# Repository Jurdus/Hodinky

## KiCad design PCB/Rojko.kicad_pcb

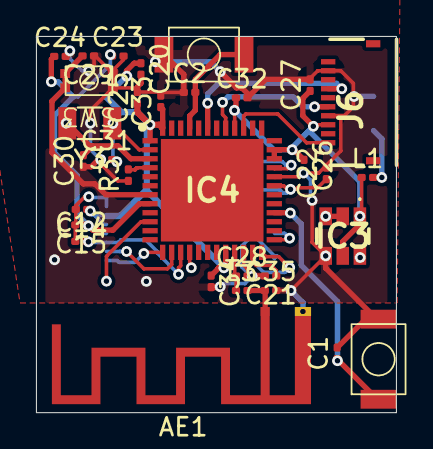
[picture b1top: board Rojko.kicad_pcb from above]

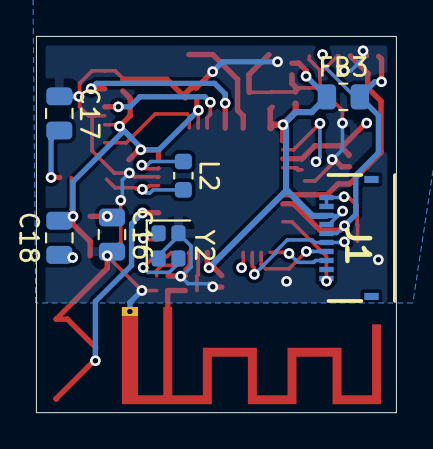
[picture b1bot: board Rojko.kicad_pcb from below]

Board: 2 copper layers, 20.0 x 20.9 mm, 39 parts (7 on the bottom side), 28 nets.

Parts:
AE1: PCB antenna; Texas_SWRA117D_2.4GHz_Right
C1, C2, C29: 100nF; C_0201_0603Metric
C12: 0.1uF; C_0201_0603Metric
C14, C15, C20, C24: 1uF; C_0201_0603Metric
C16: 10uF; C_0805_2012Metric
C17: 2x 22uF; C_0805_2012Metric
C18: 100nF; C_0805_2012Metric
C21, C25, C26, C32, C33, C34: 100n; C_0201_0603Metric
C22, C27: 4.7uF; C_0201_0603Metric
C23: 10nF; C_0201_0603Metric
C28: 0.8pF; C_0201_0603Metric
C30, C31: 10pF; C_0201_0603Metric
C35: 0.3pF; C_0201_0603Metric
FB3: 30-120Ohm@100Mhz; R_0805_2012Metric
IC3: AP63203WU-7; AP63203WU7
IC4: STM32WB35CEU6A; QFN50P700X700X60-49N-D
J1, J6: AYF-531035; AYF531035
L1: 4.9uH; L_0201_0603Metric
L2: 10uH; L_0603_1608Metric
L3: 2.7nH; L_0201_0603Metric
R3: 10k; R_0201_0603Metric
SW1, SW2: SW_MEC_5G; Switch small but not that small
SW3: SW_MEC_5G; SWITCH small
Y2: Crystal_GND24; Crystal_SMD_2016-4Pin_2.0x1.6mm
Y3: 32,768k; Crystal_SMD_3215-2Pin_3.2x1.5mm

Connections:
+3.3V: C14.1, C18.2, C20.1, C25.1, C26.1, C27.1, C32.1, C33.1, C34.1, FB3.1, IC3.1 (FB), IC3.5 (SW), IC4.1 (VBAT), IC4.20 (VDD_1), IC4.34 (VDDSMPS), IC4.35 (VDD_2), IC4.40 (VDDUSB), IC4.48 (VDD_3), J1.7, J1.8, J6.3, L1.1
+3.3VA: C15.1, C23.1, C24.1, FB3.2, IC4.8 (VDDA), J1.6
+5V: C16.1, IC3.2 (EN), IC3.3 (VIN)
/RF: AE1.1 (A), C35.1, L3.2
DISP_MOSI: IC4.16 (PA7), J1.2
DISP_ON/OFF: C12.2, IC4.15 (PA6), J1.5
DISP_SCK: IC4.10 (PA1), J1.1
DISP_SCS: IC4.13 (PA4), J1.3
DISP_VCOM: IC4.14 (PA5), J1.4
GND: AE1.2 (Shield), C1.2, C2.1, C16.2, C17.1, C20.2, C21.2, C22.2, C23.2, C24.2, C25.2, C26.2, C27.2, C28.2, C29.1, C30.1, C31.1, C32.2, C33.2, C34.2, C35.2, IC3.4 (GND), IC4.22 (VSSRF), IC4.32 (VSSSMPS), J6.4, J6.9, R3.1, SW1.3 (B), SW2.1 (A), SW3.1 (A), SW3.2 (A), Y2.2, Y2.4
unnamed: C12.1, C14.2, C15.2, J1.9, J1.10
unnamed: C17.2, L1.2
unnamed: C18.1, IC3.6 (BST)
unnamed: C29.2, IC4.7 (NRST), SW3.3 (B), SW3.4 (B)
unnamed: IC4.25 (OSC_IN), Y2.1
unnamed: IC4.24 (OSC_OUT), Y2.3
unnamed: C1.1, IC4.28 (PB0), SW1.1 (A)
unnamed: C2.2, IC4.45 (PB5), SW2.3 (B)
unnamed: C31.2, IC4.2 (PC14-OSC32_IN), Y3.2
unnamed: C30.2, IC4.3 (PC15-OSC32_OUT), Y3.1
unnamed: IC4.4 (PH3-BOOT0), R3.2
unnamed: C28.1, IC4.21 (RF1), L3.1
unnamed: C21.1, IC4.23 (VDDRF)
unnamed: C22.1, IC4.31 (VFBSMPS), L2.2
unnamed: IC4.33 (VLXSMPS), L2.1
PROG_SWCLK: IC4.41 (PA14), J6.5
PROG_SWDIO: IC4.39 (PA13), J6.1
PROG_SWO: IC4.43 (PB3), J6.7

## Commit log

2025-09-02 start
2025-09-02 rename
2025-09-02 ble add
2025-09-08 zmena chipu
2025-09-09 adda
2025-09-10 plostica
